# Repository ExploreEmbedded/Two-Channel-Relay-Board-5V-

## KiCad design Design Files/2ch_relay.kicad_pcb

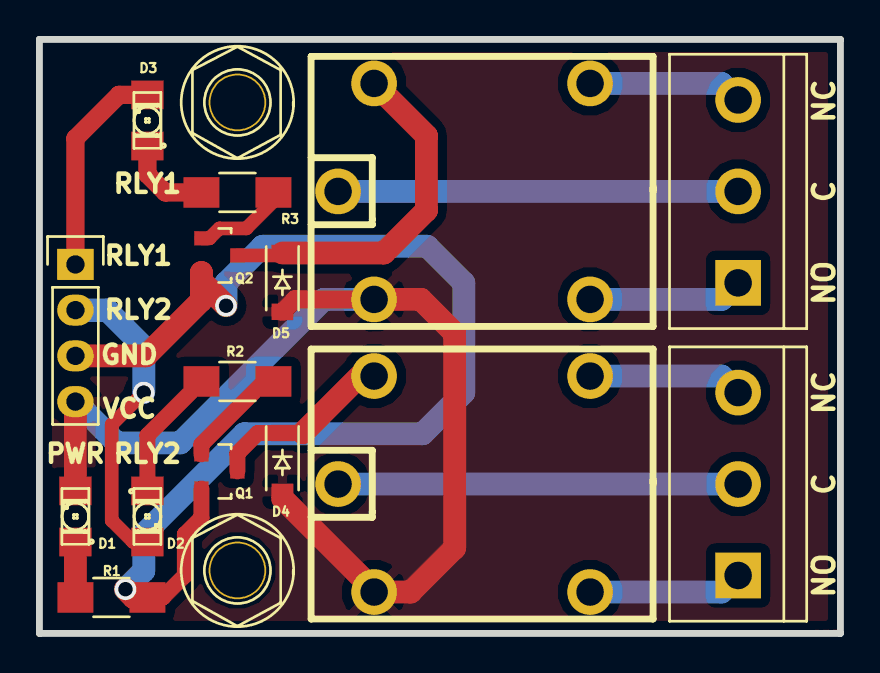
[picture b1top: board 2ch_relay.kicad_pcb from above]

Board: 2 copper layers, 44.5 x 33.0 mm, 18 parts (1 on the bottom side), 17 nets.

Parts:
D1, D2, D3: LED; LED-1206_NEW
D4, D5: IN4007; SOD-123
K1, K2: RELAY1_xl; XL-RELAY-12
K3, K4: CONN_3; bornier3
P1: CONN_4; Pin_Header_Straight_1x04
P2, P3: CONN_01X01; M3_mounting
P4: CONN_01X01; Logo_8
Q1, Q2: BC849; SOT-23
R1, R2, R3: 1K; R_1206_HandSoldering

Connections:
GND: P1.3, Q1.2, Q2.2, R1.2
unnamed: D1.1, D4.2, D5.2, K1.5, K2.5, P1.4
unnamed: D1.2, R1.1
unnamed: D2.1, P1.2
unnamed: D2.2, R2.1
unnamed: D3.1, P1.1
unnamed: D3.2, R3.1
unnamed: D4.1, K1.1, Q1.3
unnamed: D5.1, K2.1, Q2.3
unnamed: K1.2, K3.2
unnamed: K1.3, K3.3
unnamed: K1.4, K3.1
unnamed: K2.2, K4.2
unnamed: K2.3, K4.3
unnamed: K2.4, K4.1
unnamed: Q1.1, R2.2
unnamed: Q2.1, R3.2

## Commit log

2016-09-08 Added design files
